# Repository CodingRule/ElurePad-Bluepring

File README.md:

# ElurePad-Bluepring
Started the project on 28th of November 2025

This project is meant for the Bluepring Competition!

# BOM

| ID | Component                                     | QTY        | PRICE       |
|----|-----------------------------------------------|------------|------------:|
| 1  | Speed XIAO RP2040                             | 1 piece    |kit          |
| 2  | Through-hole 1N4148 diode                     | 10 pieces  |kit          |
| 3  | MX-style switch                               | 10 pieces  |kit          |
| 4  | 0.91 inch OLED display (GND-VCC-SCL-SDA)      | 1 piece    |kit          |
| 5  | Blank DSA keycap (white)                      | 11 pieces  |kit          |
| 6  | M3x16mm screw                                 | 11 pieces  |kit          |
| 7  | M3 inserts                                    | 11 pieces  |kit          |
| 8  | 3D printed case                               | 1 piece    |kit          |
| 9  | Custom PCB grant (LeadFree)                   | 5 pieces   |4.80$        |

# GO TO JOURNAL.md For journal and images
[JOURNAL.md](JOURNAL.md)

#FOR BOM

[bom.csv](bom.csv)

PHOTOS

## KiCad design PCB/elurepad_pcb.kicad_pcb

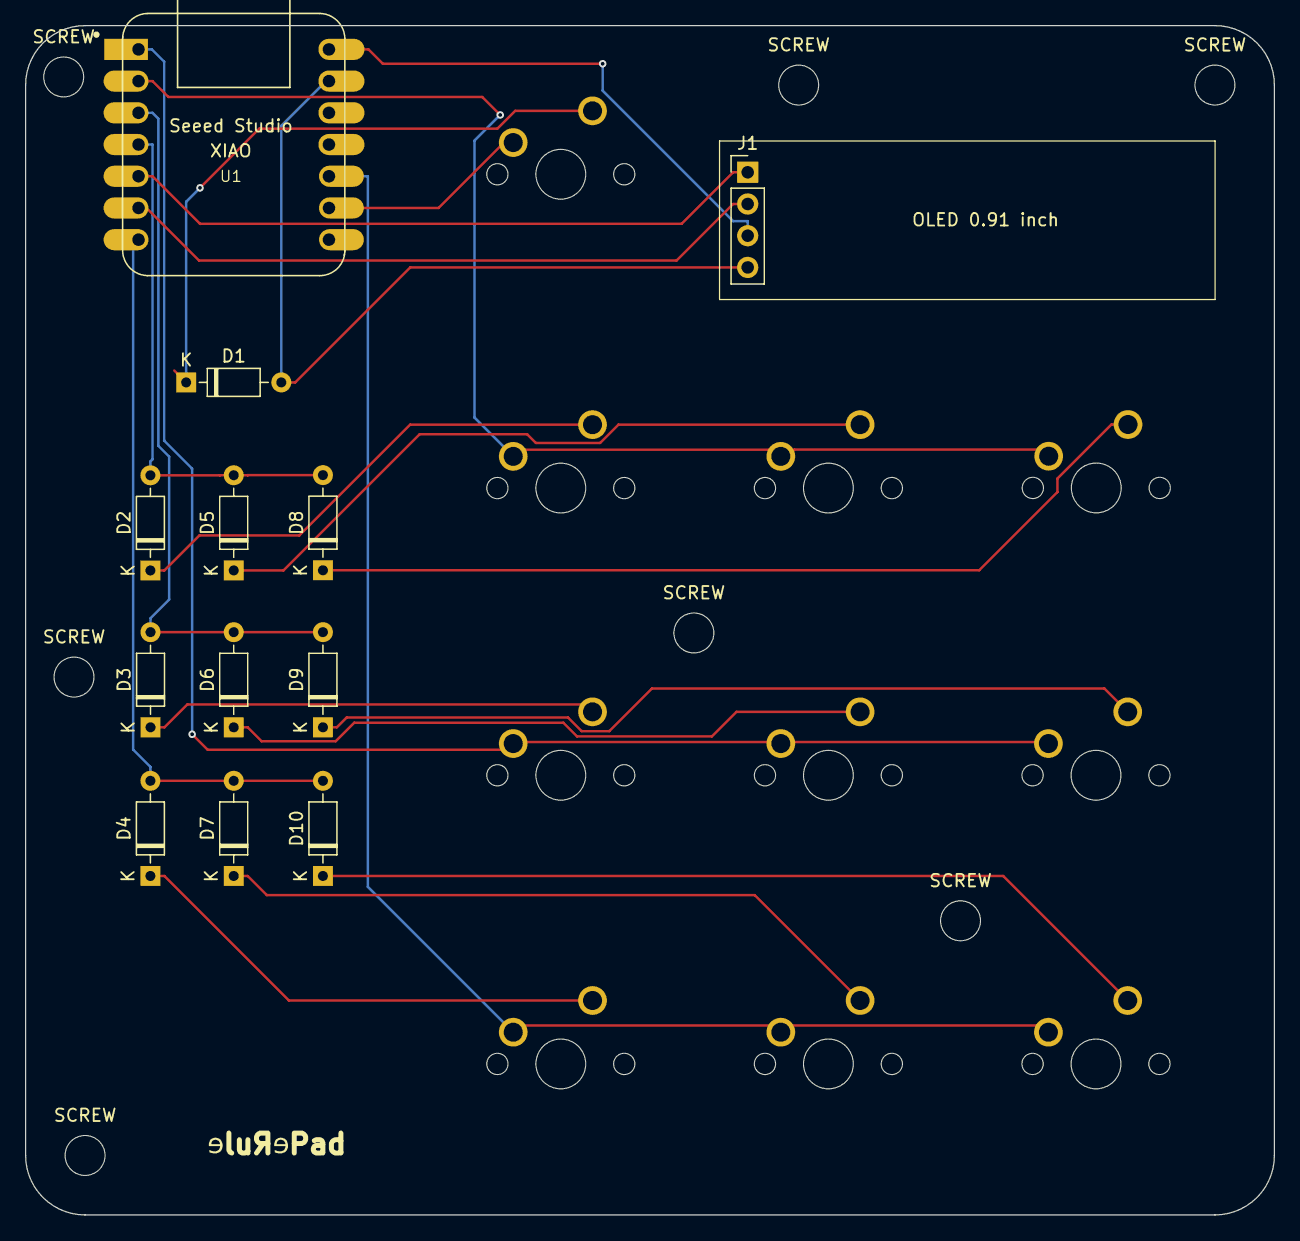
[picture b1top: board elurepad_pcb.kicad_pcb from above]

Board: 2 copper layers, 100.0 x 95.3 mm, 29 parts (0 on the bottom side), 21 nets.

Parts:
D1, D2, D3, D4, D5, D6, D7, D8, D9, D10: D; D_DO-35_SOD27_P7.62mm_Horizontal
J1: OLED_DISPLAY; PinHeader_1x04_P2.54mm_Vertical
SCREW: MountingHole_3.2mm_M3
SCREW#2, SCREW#3, SCREW#4, SCREW#5, SCREW#6, SCREW#7: MountingHole_3.2mm_M3
SW1, SW2, SW3, SW4, SW5, SW6, SW7, SW8, SW9, SW10: SW_Push_45deg; MX-Solderable-1U
U1: Seeed Studio XIAO RP2040; XIAO-Generic-Hybrid-14P-2.54-21X17.8MM

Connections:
COL0: SW2.1, SW5.1, SW8.1, U1.2 (PA4_A1_D1)
COL1: SW3.1, SW6.1, SW9.1, U1.1 (PA02_A0_D0)
COL2: SW4.1, SW7.1, SW10.1, U1.10 (PA5_A9_D9_MISO)
GND: D1.2 (A), J1.4, U1.13 (GND)
LAYER_BTN: SW1.1, U1.9 (PA7_A8_D8_SCK)
unnamed: D1.1 (K), SW1.2
unnamed: D2.1 (K), SW2.2
unnamed: D3.1 (K), SW3.2
unnamed: D4.1 (K), SW4.2
unnamed: D5.1 (K), SW5.2
unnamed: D6.1 (K), SW6.2
unnamed: D7.1 (K), SW7.2
unnamed: D8.1 (K), SW8.2
unnamed: D9.1 (K), SW9.2
unnamed: D10.1 (K), SW10.2
ROW0: D2.2 (A), D5.2 (A), D8.2 (A), U1.4 (PA11_A3_D3)
ROW1: D3.2 (A), D6.2 (A), D9.2 (A), U1.3 (PA10_A2_D2)
ROW2: D4.2 (A), D7.2 (A), D10.2 (A), U1.7 (PB08_A6_D6_TX)
SCL: J1.2, U1.6 (PA9_A5_D5_SCL)
SDA: J1.1, U1.5 (PA8_A4_D4_SDA)
VCC: J1.3, U1.14 (5V)

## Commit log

2025-11-30 Initial commit of ElurePad project
2025-11-30 Enhance README with links and images
    Added links and images to README for better documentation.
2025-12-01 Add Custom PCB grant to BOM
2025-12-01 Remove space before PRICE column in bom.csv
2025-12-01 Update PCB grant details and image in README
2025-12-01 Clean up bom.csv formatting
    Removed spaces before commas and adjusted price format.
2025-12-03 Fix component name from 'Seeed' to 'Speed'
